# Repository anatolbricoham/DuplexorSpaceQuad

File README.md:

# Diplexor 2 m / 70 cm: PCB y caja imprimible (SMA y BNC)

Diplexor pasivo que separa las bandas de **2 m (144–146 MHz)** y **70 cm (430–440 MHz)** de un único conector de radio. Hay dos versiones que solo se diferencian en los conectores (**SMA** o **BNC**). Cada una tiene su PCB de 2 capas y su caja para impresora 3D, diseñada lo más compacta posible.

| | SMA | BNC |
|---|---|---|
| PCB | 37 × 23 mm | 55.5 × 33 mm |
| Caja (exterior) | **45.2 × 27.6 × 14.1 mm** | **59.9 × 37.6 × 23.5 mm** |
| Conector | Amphenol 132289 (canto, bulkhead) | Amphenol B6252HB-NPP3G-50 (acodado) |
| Tornillos | 2 × M2 × 10 autorroscantes | 2 × M2 × 12 autorroscantes |

## Circuito

- **2 m:** paso bajo formado por L1 68 nH, C1 18 pF, L2 100 nH, C2 18 pF y L3 68 nH.
- **70 cm:** paso alto formado por C3, L4 15 nH, C4, L5 15 nH y C5.

En el esquema original, el valor de C1/C2 es ambiguo (10 o 18 pF). Se ha usado **18 pF** porque con 10 pF la rama de 2 m queda desadaptada.

### Valores recomendados
Con los valores del esquema (C3 = C5 = 4.7 pF, C4 = 2.7 pF), la rama de 70 cm queda mal adaptada (S11 ≈ −6.4 dB, ROE ≈ 2.8). Con **C3 = C5 = 8.2 pF y C4 = 4.7 pF** mejora mucho. Se usan las mismas huellas:

| Simulación (ideal) | Esquema | Optimizado |
|---|---|---|
| S11 a 145 MHz | −19 dB | −31 dB |
| S11 a 435 MHz | −7 dB | −31 dB |
| Pérdida de inserción | 0.05 / 0.9 dB | < 0.05 dB |
| Aislamiento entre 2m y 70cm | > 50 dB | > 49 dB |

Puedes reproducirla con `make sim`.

## Estructura del repositorio
```
hardware/{SMA,BNC}/        Proyecto KiCad 7 (.kicad_pcb/.kicad_pro) + board_geometry.json
fabrication/{SMA,BNC}/     Gerber, taladros, zip para el fabricante, BOM, pick&place, informe DRC
enclosure/diplexor_caja.scad   Caja paramétrica (OpenSCAD)
enclosure/stl/             STL listos para imprimir (base + tapa por versión)
BOM/                       Listas de materiales (fuente)
scripts/                   Generador de PCB, simulador y script de build
docs/                      Imágenes, pruebas y montaje
```

## Fabricar la PCB
Sube `fabrication/<VERSION>/gerber_diplexor_2m70cm_<VERSION>.zip` al fabricante con estos parámetros:
- 2 capas, FR4 de **1.6 mm**, cobre de 1 oz y acabado HASL o ENIG.
- Pista y separación mínimas: 0.25 / 0.2 mm. Vía: 0.4 / 0.8 mm.
- Las líneas de RF son CPWG de 50 Ω (pista de 1.4 mm con 0.25 mm de separación a masa). El grosor de 1.6 mm es necesario para mantener esa impedancia.

## Imprimir la caja
- **Material:** PETG (recomendado) o PLA. Capa de 0.2 mm, 3 perímetros, relleno del 20 % o más.
- **Orientación:** la base con el suelo sobre la cama. La tapa ya se exporta boca abajo, con el techo sobre la cama.
- No hacen falta soportes. Los semicírculos de los conectores quedan como pequeños puentes.
- Es una caja "almeja": se abre a la altura del eje de los conectores. Un labio de 1.4 mm centra la tapa sobre la base.

Más detalles en [docs/MONTAJE.md](docs/MONTAJE.md).

> **Importante:** las medidas de los conectores de la caja (brida del SMA, altura y frontal del BNC) son estimaciones a partir de la huella de KiCad. **Mide tu conector con un calibre** y ajusta los parámetros `SMA_*` / `BNC_*` al principio de `enclosure/diplexor_caja.scad` antes de imprimir la versión final. También conviene imprimir primero solo la base y comprobar el ajuste.

## Pruebas
Consulta el protocolo con NanoVNA en [docs/PRUEBAS.md](docs/PRUEBAS.md).

## Regenerar todo
Requisitos: KiCad 7 (`kicad-cli` y el módulo Python `pcbnew`), `gerbv`, `openscad`, `python3-numpy` y `xvfb` (para los renders).
```bash
make          # PCB + DRC + Gerber + BOM/pos + imágenes + STL
make sim      # simulación del filtro
```
Todo sale de `scripts/gen_pcb.py`. La caja lee la posición de los conectores y de los agujeros desde `hardware/*/board_geometry.json`, así que si se mueve un conector en la PCB, la caja se adapta sola.

## Limitaciones
- Con componentes 0805 admite unos **5–10 W**, suficiente para equipos portátiles o QRP. Para más potencia hay que usar bobinas al aire y condensadores de mica o ATC.
- La caja de plástico no apantalla. La PCB lleva planos de masa en las dos caras con vías de cosido. Si hace falta blindaje, se puede pintar el interior con pintura conductora o forrarlo con cinta de cobre.

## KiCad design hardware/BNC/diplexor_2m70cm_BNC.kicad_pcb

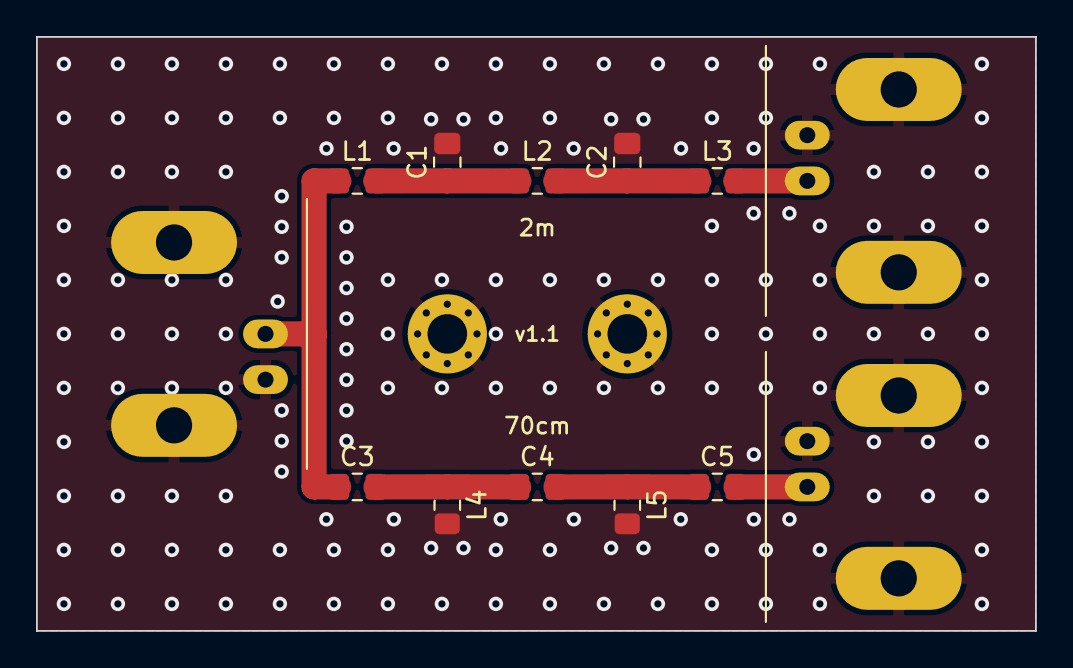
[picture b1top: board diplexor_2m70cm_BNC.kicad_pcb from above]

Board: 2 copper layers, 55.5 x 33.0 mm, 15 parts (0 on the bottom side), 8 nets.

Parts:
C1, C2: 18pF; C_0805_2012Metric_Pad1.18x1.45mm_HandSolder
C3, C5: 4.7pF; C_0805_2012Metric_Pad1.18x1.45mm_HandSolder
C4: 2.7pF; C_0805_2012Metric_Pad1.18x1.45mm_HandSolder
H1, H2: M2; MountingHole_2.2mm_M2_Pad_Via
J1, J2, J3: BNC R/A PCB (Amphenol B6252HB-NPP3G-50); BNC_Amphenol_B6252HB-NPP3G-50_Horizontal
L1, L3: 68nH; L_0805_2012Metric_Pad1.15x1.40mm_HandSolder
L2: 100nH; L_0805_2012Metric_Pad1.15x1.40mm_HandSolder
L4, L5: 15nH; L_0805_2012Metric_Pad1.15x1.40mm_HandSolder

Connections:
GND: C1.2, C2.2, H1.1, H2.1, J1.2, J2.2, J3.2, L4.2, L5.2
N1: C1.1, L1.2, L2.1
N2: C2.1, L2.2, L3.1
N3: C3.2, C4.1, L4.1
N4: C4.2, C5.1, L5.1
OUT_2M: J2.1, L3.2
OUT_70CM: C5.2, J3.1
RADIO: C3.1, J1.1, L1.1

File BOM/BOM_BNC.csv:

Ref,Cant,Valor (esquema),Valor optimizado (recomendado),Encapsulado,Tipo recomendado
L1 L3,2,68nH,68nH,0805,Inductor cerámico alta Q (p.ej. Coilcraft 0805CS-680XJL)
L2,1,100nH,100nH,0805,Inductor cerámico alta Q (p.ej. Coilcraft 0805CS-101XJL)
L4 L5,2,15nH,15nH,0805,Inductor cerámico alta Q (p.ej. Coilcraft 0805CS-150XJL)
C1 C2,2,18pF,18pF,0805,C0G/NP0 >=100V alta Q
C3 C5,2,4.7pF,8.2pF,0805,C0G/NP0 >=100V alta Q
C4,1,2.7pF,4.7pF,0805,C0G/NP0 >=100V alta Q
J1 J2 J3,3,BNC,,,Amphenol B6252HB-NPP3G-50 (BNC hembra; ángulo recto; PCB)
H1 H2,2,M2,,,Taladro 2.2 mm metalizado a masa
CAJA,1,,,,Caja impresa 3D (enclosure/stl/caja_bnc_base.stl + _tapa.stl)
TORNILLO,2,,,,M2 cabeza cilíndrica/alomada autorroscante: M2x12
